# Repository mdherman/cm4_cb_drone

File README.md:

# cm4_cb_drone

Carrier board for a Raspberri Compute Module 4 to be placed inside a drone, and communicating with a Pixhawk 4 mini over UART.

WARNING: This board is not tested yet!

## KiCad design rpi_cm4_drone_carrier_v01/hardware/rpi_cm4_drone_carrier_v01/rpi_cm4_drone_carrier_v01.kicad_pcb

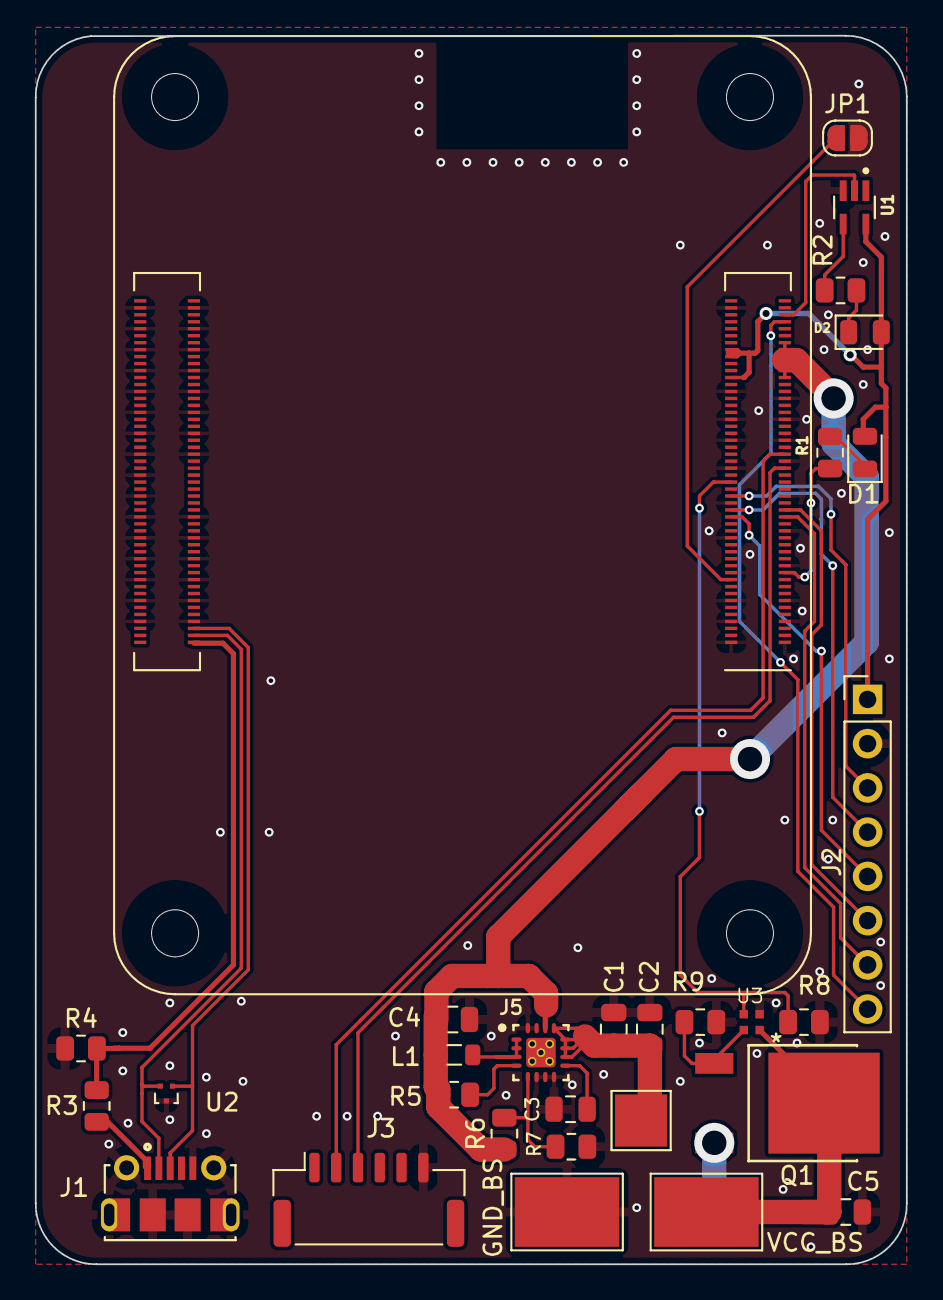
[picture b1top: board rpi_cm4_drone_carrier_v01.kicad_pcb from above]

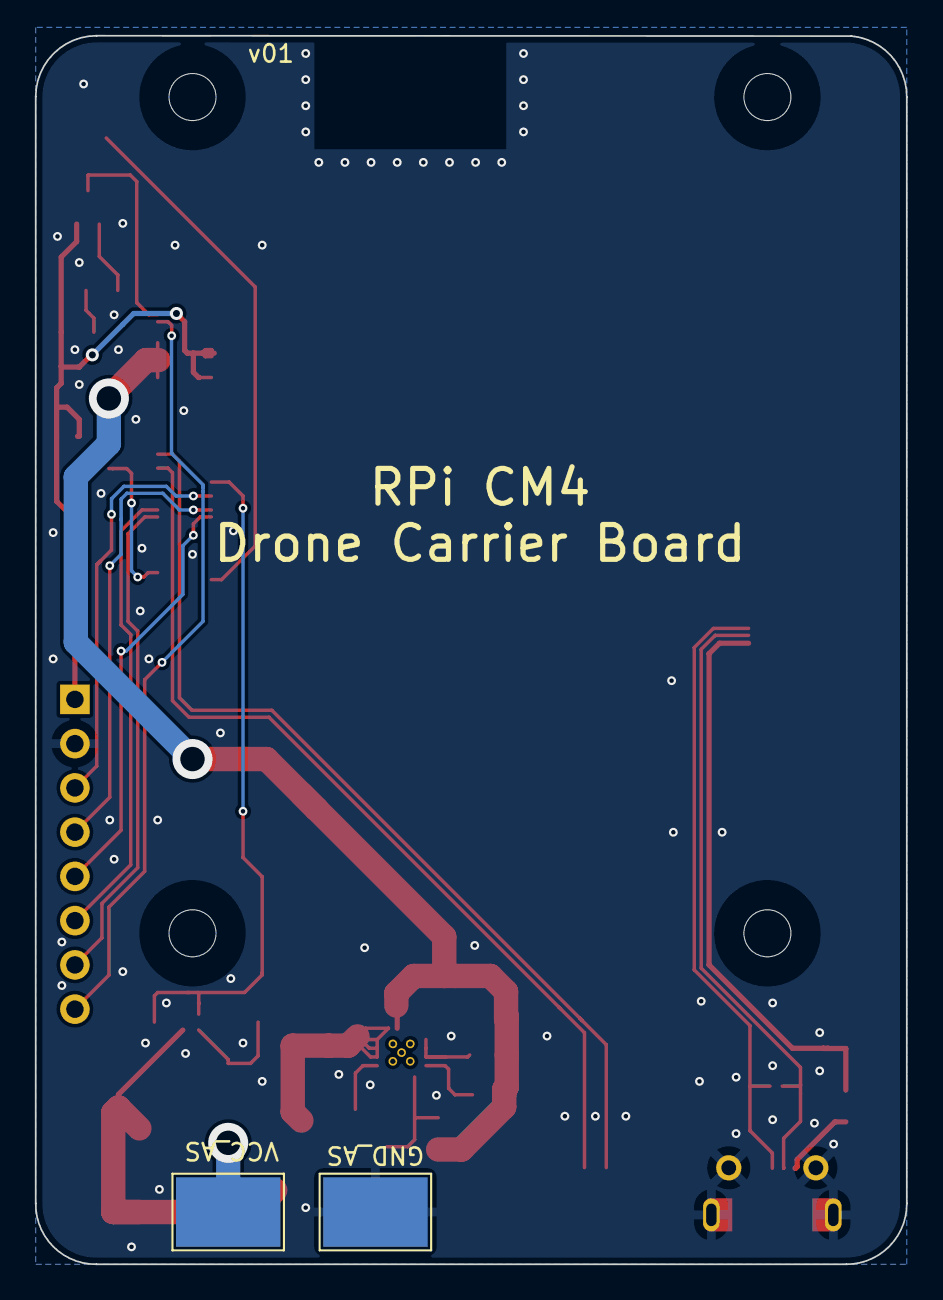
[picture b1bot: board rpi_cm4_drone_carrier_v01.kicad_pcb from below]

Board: 2 copper layers, 50.0 x 70.5 mm, 29 parts (2 on the bottom side), 30 nets.

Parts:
C1: 10uF; C_0805_2012Metric
C2: 0.1uF; C_0805_2012Metric
C3: 3.3nF; C_0805_2012Metric
C4: 22uF; C_0805_2012Metric
C5: 4.7uF; C_0805_2012Metric
D1: LED Green; LED_0805_2012Metric
D2: LED Red; LED_0805_2012Metric
GND_AS: GND_PAD
J1: 105017-1001; MOLEX_105017-1001
J2: GPIO; PinHeader_1x08_P2.54mm_Vertical
J3: JST_SM06B; JST_GH_SM06B-GHS-TB_1x06-1MP_P1.25mm_Horizontal
J5: TPS62133RGTR; Texas_Instruments-TPS62133RGTR-Manufacturer_Recommended
JP1: SolderJumper_2_Open; SolderJumper-2_P1.3mm_Open_RoundedPad1.0x1.5mm
L1: 2.2uH; L_0805_2012Metric
Module1: ComputeModule4-CM4; Raspberry-Pi-4-Compute-Module
Q1: IPD50N03S2L06ATMA1; Trans_Infineon_IPD50N03S2L06ATMA1
R1, R2: 1k; R_0805_2012Metric
R3, R4: 2.2K; R_0805_2012Metric
R5, R8, R9: 100K; R_0805_2012Metric
R6: 261K; R_0805_2012Metric
R7: 51K; R_0805_2012Metric
U1: SN74LVC1G07DCKR; SOT65P210X110-5N
U2: TPD2EUSB30; Texas_DRT-3
U3: MIC5019YFT-TR
VCC_AS: VCC_PAD

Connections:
+3.3V: D1.2 (A), D2.2 (A), J2.1, Module1.78 (GPIO_VREF(1.8v/3.3v_Input)), Module1.84 (+3.3v_(Output)), Module1.86 (+3.3v_(Output)), U1.5 (VCC)
+5V: C4.1, J5.14 (VOS), L1.2, Module1.77 (+5v_(Input)), Module1.79 (+5v_(Input)), Module1.81 (+5v_(Input)), Module1.83 (+5v_(Input)), Module1.85 (+5v_(Input)), Module1.87 (+5v_(Input)), R5.1, R6.1
+7.4V: Q1.3 (source), VCC_AS.VCC
+7.4V AFS: C1.1, C2.1, J5.10 (AVIN), J5.11 (PVIN), J5.12 (PVIN), J5.13 (EN)
+7.4V BS: C5.1, Q1.4 (drain), U3.1 (VDD)
/CM4 GPIO/EEPROM_nWP: JP1.1 (A), Module1.20 (EEPROM_nWP)
/CM4 GPIO/GPIO7: J2.7, Module1.37 (GPIO7)
/CM4 GPIO/GPIO8: J2.6, Module1.39 (GPIO8)
/CM4 GPIO/GPIO9: J2.4, Module1.40 (GPIO9)
/CM4 GPIO/GPIO10: J2.3, Module1.44 (GPIO10)
/CM4 GPIO/GPIO11: J2.5, Module1.38 (GPIO11)
/CM4 GPIO/GPIO14: J3.2 (3,3V_TX_(b)), Module1.55 (GPIO14)
/CM4 GPIO/GPIO15: J3.3 (3,3V_RX_(b)), Module1.51 (GPIO15)
/CM4 GPIO/Power_Switch_Signal: Module1.48 (GPIO27), R8.1, U3.3 (IN)
/CM4 GPIO/nLED_Activity: Module1.21 (PI_nLED_Activity), R1.2
/CM4 GPIO/nPWR_LED: Module1.95 (nPI_LED_PWR), U1.2 (A)
/CM4 GPIO/nRPIBOOT: J2.8, Module1.93 (nRPIBOOT)
/CM4 High Speed/USB2_N: J1.2, Module1.103 (USB2_N), U2.2 (D-)
/CM4 High Speed/USB2_P: J1.3, Module1.105 (USB2_P), U2.1 (D+)
/CM4 High Speed/USB_OTG_ID: Module1.101 (USB_OTG_ID), R3.2, R4.1
GND: C1.2, C2.2, C3.2, C4.2, C5.2, GND_AS.GND, J1.5, J1.S1 (SHIELD), J1.S2 (SHIELD), J1.S3 (SHIELD), J1.S4 (SHIELD), J1.S5 (SHIELD), J1.S6 (SHIELD), J2.2, J3.6 (GND_(b)), J5.6 (AGND), J5.7 (FSW), J5.8 (DEF), J5.15 (PGND), J5.16 (PGND), JP1.2 (B), Module1.1 (GND), Module1.2 (GND), Module1.7 (GND), Module1.8 (GND), Module1.13 (GND), Module1.14 (GND), Module1.22 (GND), Module1.23 (GND), Module1.32 (GND), Module1.33 (GND), Module1.42 (GND), Module1.43 (GND), Module1.52 (GND), Module1.53 (GND), Module1.59 (GND), Module1.60 (GND), Module1.65 (GND), Module1.66 (GND), Module1.71 (GND), Module1.74 (GND), Module1.98 (GND), Module1.107 (GND), Module1.108 (GND), Module1.113 (GND), Module1.114 (GND), Module1.119 (GND), Module1.120 (GND), Module1.125 (GND), Module1.126 (GND), Module1.131 (GND), Module1.132 (GND), Module1.137 (GND), Module1.138 (GND), Module1.144 (GND), Module1.150 (GND), Module1.155 (GND), Module1.156 (GND), Module1.161 (GND), Module1.162 (GND), Module1.167 (GND), Module1.168 (GND), Module1.173 (GND), Module1.174 (GND), Module1.179 (GND), Module1.180 (GND), Module1.185 (GND), Module1.186 (GND), Module1.191 (GND), Module1.192 (GND), Module1.197 (GND), Module1.198 (GND), R4.2, R7.2, R8.2, R9.2, U1.3 (GND), U2.3 (GND), U3.2 (GND)
unnamed: C3.1, J5.9 (SS/TR)
unnamed: D1.1 (K), R1.1
unnamed: D2.1 (K), R2.1
unnamed: J1.1, R3.1
unnamed: J5.1 (SW), J5.2 (SW), J5.3 (SW), L1.1
unnamed: J5.4 (PG), R5.2
unnamed: J5.5 (FB), R6.2, R7.1
unnamed: Q1.1 (gate), R9.1, U3.4 (OUT)
unnamed: R2.2, U1.4 (Y)

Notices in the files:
rpi_cm4_drone_carrier_v01/hardware/rpi_cm4_drone_carrier_v01/rpi_cm4_drone_carrier_v01.kicad_pcb:
creativecommons.org/licenses/by/4.0
License: CC BY 4.0
parts and their libraries:
Copyright 2016 Accelerated Designs. All rights reserved.
